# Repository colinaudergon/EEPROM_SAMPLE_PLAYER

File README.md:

# EEPROM_SAMPLE_PLAYER

This project is my first attempt at reading and writting data to a EEPROM. The EEPROM countais a variety of 8bit samples(These are created using a Python script that will be attached soon).
The data stored in the EEPROM are accessed using two shift registers (SIPO). The output of the memory are read directly.
The audio implementation is (for now) based on the Auduino code, as I'm still wrapping my head around audio generation with uC.

By all mean, this is a first prototype, and for sure will need refinement.

C.A

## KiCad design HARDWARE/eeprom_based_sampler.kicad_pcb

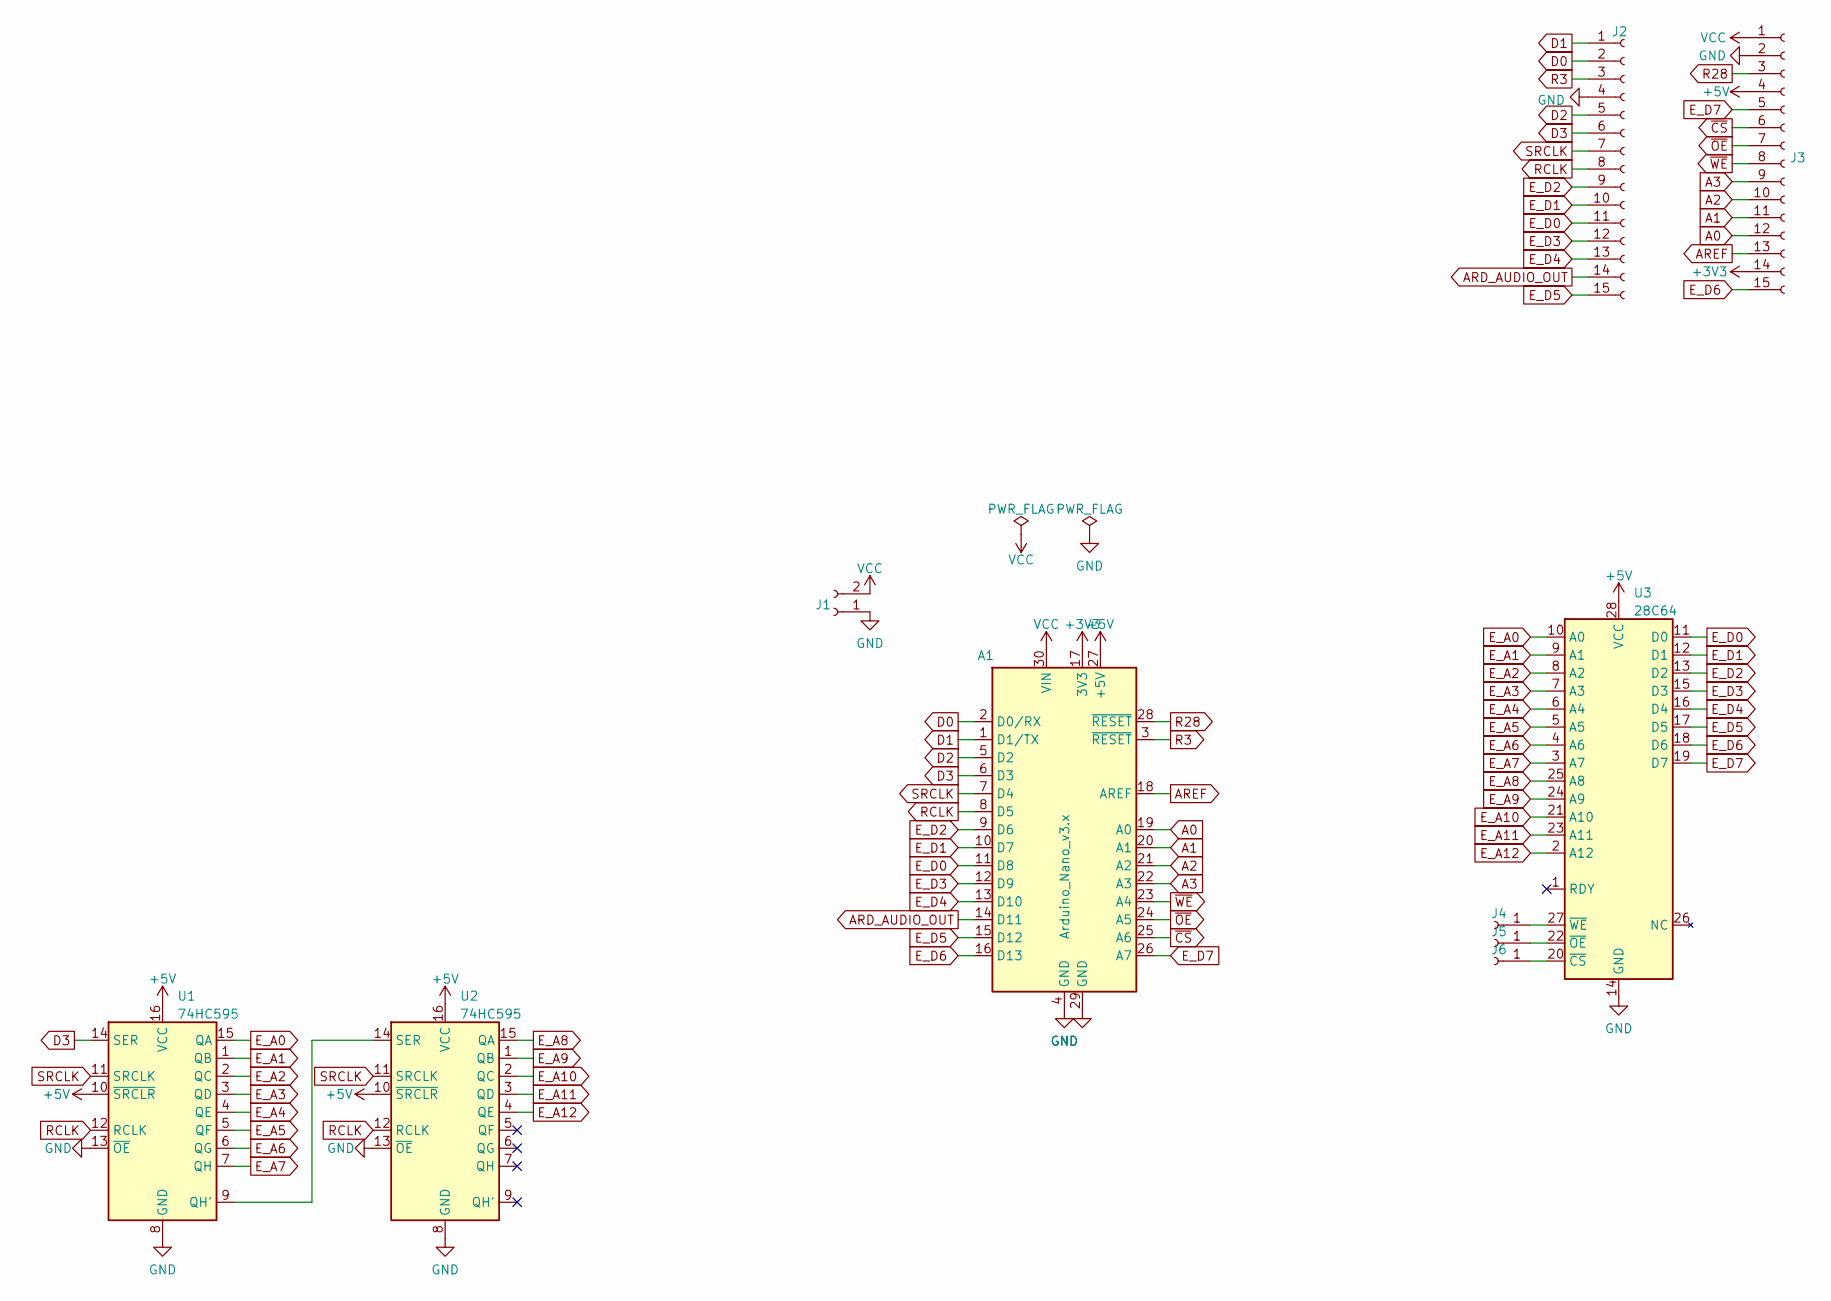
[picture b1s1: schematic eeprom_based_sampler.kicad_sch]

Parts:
A1: Arduino_Nano_v3.x; Arduino_Nano
J1: Conn_01x02_Female; PinSocket_1x02_P2.54mm_Vertical
J2, J3: Conn_01x15_Female; PinSocket_1x15_P2.54mm_Vertical
J4, J5, J6: Conn_01x01_Female; PinHeader_1x01_P2.54mm_Vertical
U1, U2: 74HC595; DIP-16_W7.62mm_Socket_LongPads
U3: 28C64; DIP-28_W15.24mm_LongPads

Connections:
+3V3: A1.17 (3V3), J3.14
+5V: A1.27 (+5V), J3.4, U1.10 (~SRCLR), U1.16 (VCC), U2.10 (~SRCLR), U2.16 (VCC), U3.28 (VCC)
A0: A1.19 (A0), J3.12
A1: A1.20 (A1), J3.11
A2: A1.21 (A2), J3.10
A3: A1.22 (A3), J3.9
ARD_AUDIO_OUT: A1.14 (D11), J2.14
AREF: A1.18 (AREF), J3.13
D0: A1.2 (D0/RX), J2.2
D1: A1.1 (D1/TX), J2.1
D2: A1.5 (D2), J2.5
D3: A1.6 (D3), J2.6, U1.14 (SER)
E_A0: U1.15 (QA), U3.10 (A0)
E_A1: U1.1 (QB), U3.9 (A1)
E_A2: U1.2 (QC), U3.8 (A2)
E_A3: U1.3 (QD), U3.7 (A3)
E_A4: U1.4 (QE), U3.6 (A4)
E_A5: U1.5 (QF), U3.5 (A5)
E_A6: U1.6 (QG), U3.4 (A6)
E_A7: U1.7 (QH), U3.3 (A7)
E_A8: U2.15 (QA), U3.25 (A8)
E_A9: U2.1 (QB), U3.24 (A9)
E_A10: U2.2 (QC), U3.21 (A10)
E_A11: U2.3 (QD), U3.23 (A11)
E_A12: U2.4 (QE), U3.2 (A12)
E_D0: A1.11 (D8), J2.11, U3.11 (D0)
E_D1: A1.10 (D7), J2.10, U3.12 (D1)
E_D2: A1.9 (D6), J2.9, U3.13 (D2)
E_D3: A1.12 (D9), J2.12, U3.15 (D3)
E_D4: A1.13 (D10), J2.13, U3.16 (D4)
E_D5: A1.15 (D12), J2.15, U3.17 (D5)
E_D6: A1.16 (D13), J3.15, U3.18 (D6)
E_D7: A1.26 (A7), J3.5, U3.19 (D7)
GND: A1.4 (GND), A1.29 (GND), J1.1, J2.4, J3.2, U1.8 (GND), U1.13 (~OE), U2.8 (GND), U2.13 (~OE), U3.14 (GND)
unnamed: U1.9 (QH'), U2.14 (SER)
unnamed: J6.1, U3.20 (~CS)
unnamed: J5.1, U3.22 (~OE)
unnamed: J4.1, U3.27 (~WE)
R3: A1.3 (~RESET), J2.3
R28: A1.28 (~RESET), J3.3
RCLK: A1.8 (D5), J2.8, U1.12 (RCLK), U2.12 (RCLK)
SRCLK: A1.7 (D4), J2.7, U1.11 (SRCLK), U2.11 (SRCLK)
VCC: A1.30 (VIN), J1.2, J3.1
~CS: A1.25 (A6), J3.6
~OE: A1.24 (A5), J3.7
~WE: A1.23 (A4), J3.8

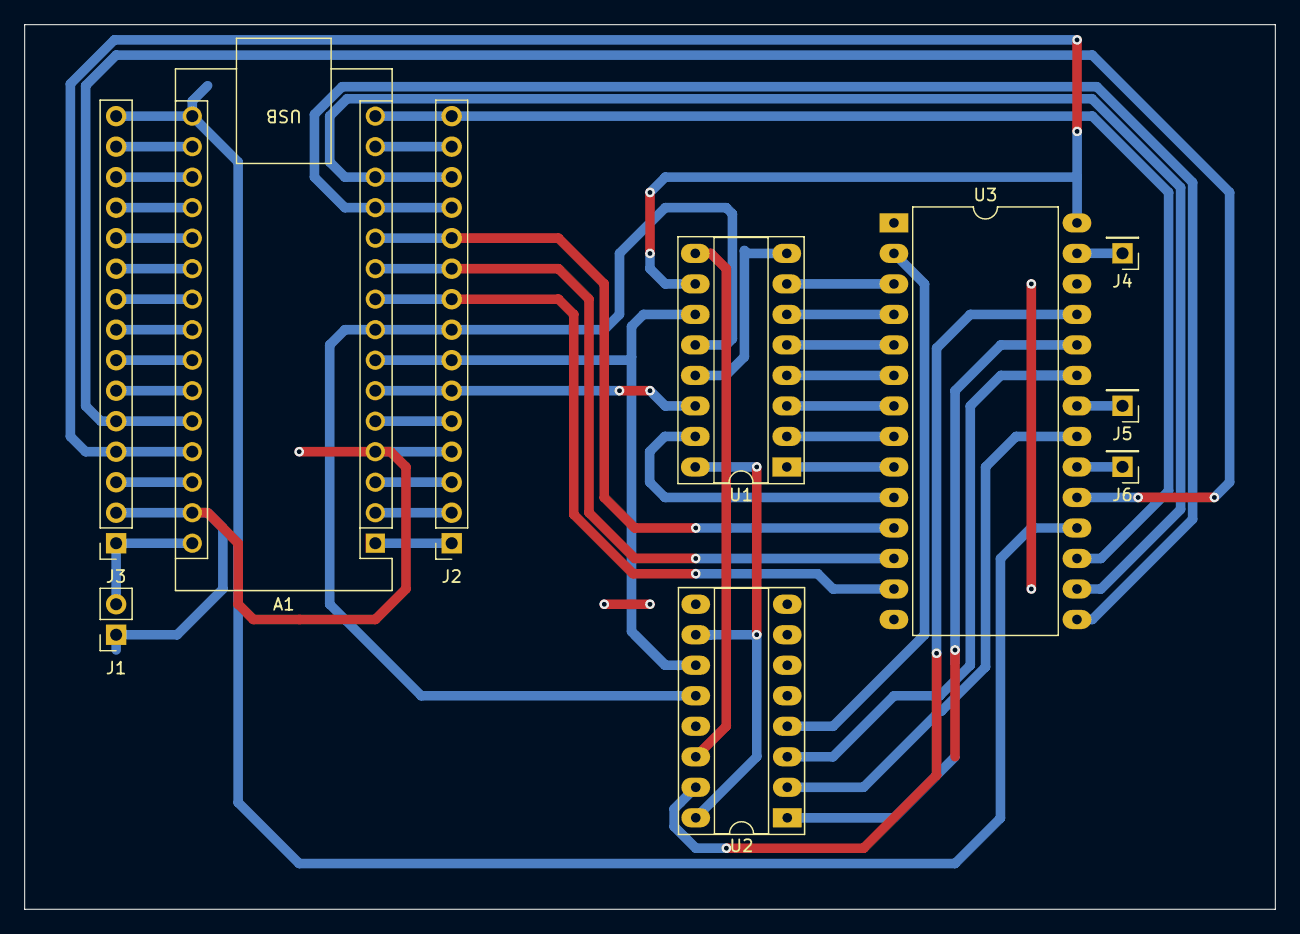
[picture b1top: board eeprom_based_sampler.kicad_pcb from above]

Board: 2 copper layers, 104.1 x 73.7 mm, 10 parts (0 on the bottom side), 46 nets.

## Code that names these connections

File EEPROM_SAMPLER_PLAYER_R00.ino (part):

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#include <avr/pgmspace.h>

//SHIFT REGISTER CONNECTION
#define SRCLK 4 // D4 Clock pin
#define RCLK 5 //D5 Latch pin
#define SER 3 //D3

//EEPROM CONNECTION
#define E_D0 8//D8
#define E_D1 7 //D7
#define E_D2 6 //D6
#define E_D3 9//D9
#define E_D4 10//D10
#define E_D5 12//D12
#define E_D6 13 //D13
#define E_D7 A7 //A7

#define WE A4
#define OE A5
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void setup() {

  //SHIFT REGISTER
  pinMode(SRCLK, OUTPUT);
  pinMode(RCLK, OUTPUT);
  pinMode(SER, OUTPUT);

  //SHIFT REGISTER
  pinMode(SRCLK, OUTPUT);
  pinMode(RCLK, OUTPUT);
  pinMode(SER, OUTPUT);

  //EEPROM CONNECTION
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
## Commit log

2023-04-18 Create gitkeep
